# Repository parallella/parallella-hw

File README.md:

PARALLELLA: Supercomputing for Everyone
========================================	

This repository contains open source board and FPGA designs associated with the Parallella project. 

## Directory

Board                                | Description                | CAD       | Status     |
-------------------------------------|----------------------------|-----------|------------|
[parallella](parallella/README.md)   | Parallella                 | Cadence   | Production |
[porcupine](porcupine/README.md)     | Parallella Breakout Board  | KiCad     | Production |
[meta](meta)                         | Epiphany 4096-core System  | Cadence   | Prototype  |
[buddy](buddy)                       | Epiphany-V Evaluation Board| Cadence   | Prototype  |
[paracase](paracase)                 | Aluminum Case              | SolidWorks| Production |
[parasdr](parasdr/README.md)         | SDR adapter Board          | Cadence   | Production |
[kvision](kvision/README.md)         | Stereo Vision Board        | Altium    | Prototype  |
[paralime](paralime)                 | Myriad-RF daughter Board   | KiCad     | Prototype  |
[paracluster](paracluster/README.md) | Cluster Board              | N/A       | Prototype  |
[paralib](paralib)                   | CAD librares               | Various   | Prouction  |
[paratemplate](paratemplate)         | Daugher Card Template      | KiCad     | Production |
[paratile](paratile/README.md)       | Breakout Board             | Eagle     | Prototype  |
[aafm](aafm/README.md)               | Epiphany-III FMC Board     | KiCad     | Production |
[archive](archive)                   | Old Parallella stuff       | N/A       | Obsolete   |

## FPGA Design Sources
All Parallella related FPGA sources have been moved to the [OH! library](https://github.com/parallella/oh) library and released under MIT license.

## License
Board design files are released under the Creative Common Share Alike license unlesss otherwise specified.

## How to do a pull-request

1. Fork this repository to your personal github account using the 'fork' button 2. above
3. Clone your 'parallella-hw' fork to a local computer using 'git clone'
4. Create a new sub-directory at the root of the repo
5. Add your project files with the appropriate license clearly stated
6. Add a README.md file (see the skeleton directory for a template)
7. Use git add-->git commit-->git push to add changes to your fork of 'parallella-examples'
8. Submit a pull request by clicking the 'pull request' button on YOUR github 'parallella-examples' repo.

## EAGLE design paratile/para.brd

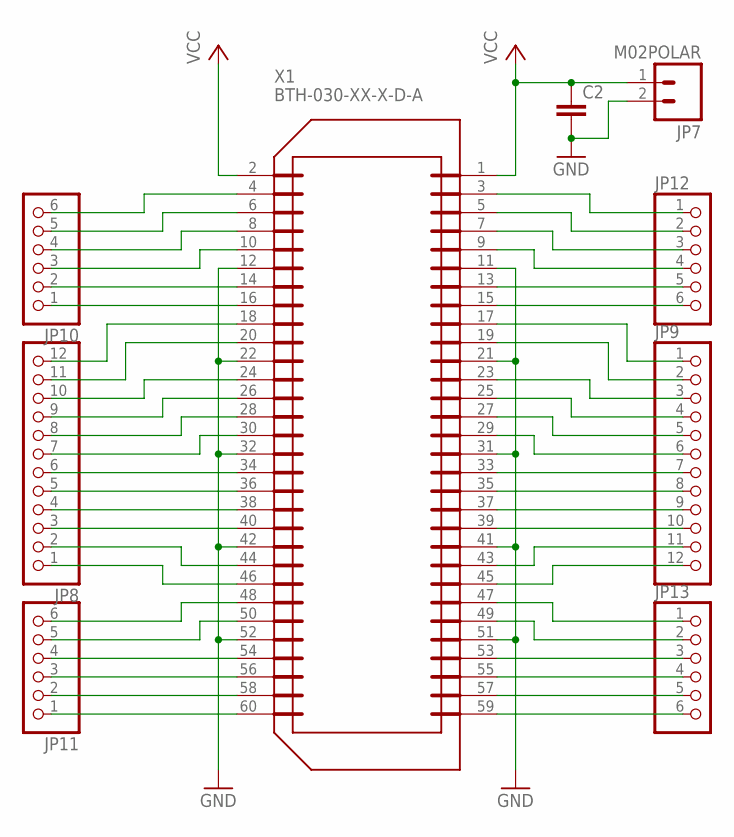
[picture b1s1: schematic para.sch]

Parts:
C2: CAP0805; 0805
JP7: M02POLAR; MOLEX-1X2
JP8, JP9: PINHD-1X12-CB; 1X12-CB
JP10, JP11, JP12, JP13: PINHD-1X6CB; 1X06-CLEANBIG
X1: BTH-030-XX-X-D-A

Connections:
GND: C2.2, JP7.2, X1.11, X1.12, X1.21, X1.22, X1.31, X1.32, X1.41, X1.42, X1.51, X1.52
GPIO0_N: JP12.1, X1.3
GPIO0_P: JP12.2, X1.5
GPIO1_N: JP10.6, X1.4
GPIO1_P: JP10.5, X1.6
GPIO2_N: JP12.3, X1.7
GPIO2_P: JP12.4, X1.9
GPIO3_N: JP10.4, X1.8
GPIO3_P: JP10.3, X1.10
GPIO4_N: JP12.5, X1.13
GPIO4_P: JP12.6, X1.15
GPIO5_N: JP10.2, X1.14
GPIO5_P: JP10.1, X1.16
GPIO6_N: JP9.1, X1.17
GPIO6_P: JP9.2, X1.19
GPIO7_N: JP8.12, X1.18
GPIO7_P: JP8.11, X1.20
GPIO8_N: JP9.3, X1.23
GPIO8_P: JP9.4, X1.25
GPIO9_N: JP8.10, X1.24
GPIO9_P: JP8.9, X1.26
GPIO10_N: JP9.5, X1.27
GPIO10_P: JP9.6, X1.29
GPIO11_N: JP8.8, X1.28
GPIO11_P: JP8.7, X1.30
GPIO12_N: JP9.7, X1.33
GPIO12_P: JP9.8, X1.35
GPIO13_N: JP8.6, X1.34
GPIO13_P: JP8.5, X1.36
GPIO14_N: JP9.9, X1.37
GPIO14_P: JP9.10, X1.39
GPIO15_N: JP8.4, X1.38
GPIO15_P: JP8.3, X1.40
GPIO16_N: JP9.11, X1.43
GPIO16_P: JP9.12, X1.45
GPIO17_N: JP8.2, X1.44
GPIO17_P: JP8.1, X1.46
GPIO18_N: JP13.1, X1.47
GPIO18_P: JP13.2, X1.49
GPIO19_N: JP11.6, X1.48
GPIO19_P: JP11.5, X1.50
GPIO20_N: JP13.3, X1.53
GPIO20_P: JP13.4, X1.55
GPIO21_N: JP11.4, X1.54
GPIO21_P: JP11.3, X1.56
GPIO22_N: JP13.5, X1.57
GPIO22_P: JP13.6, X1.59
GPIO23_N: JP11.2, X1.58
GPIO23_P: JP11.1, X1.60
VCC: C2.1, JP7.1, X1.1, X1.2

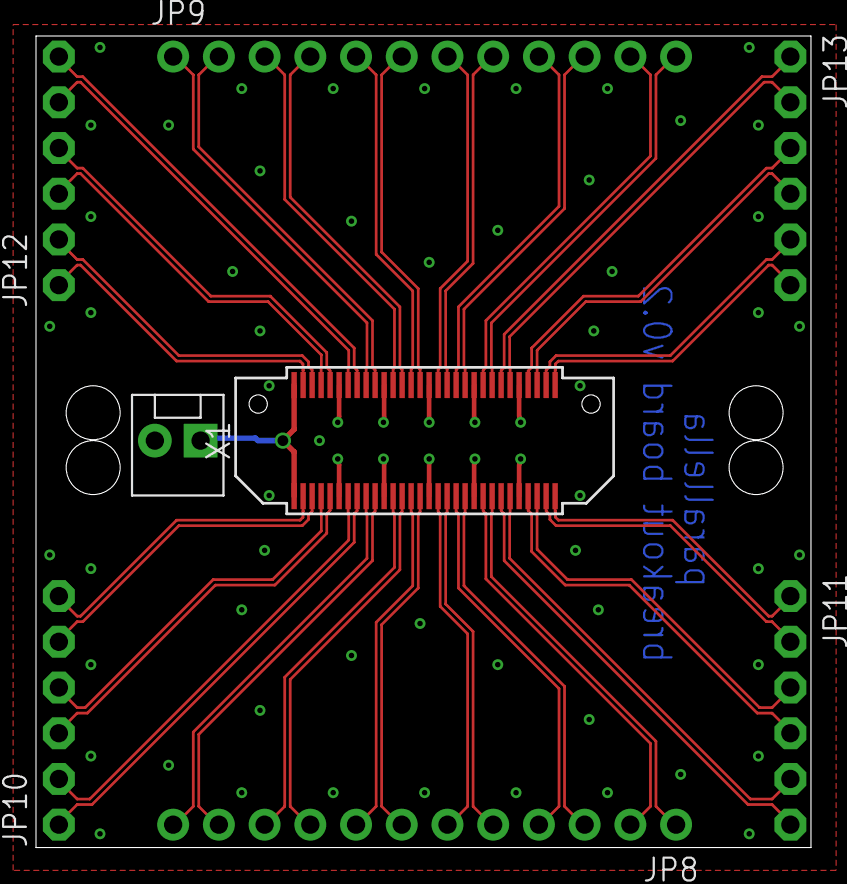
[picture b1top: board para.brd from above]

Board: 2 copper layers, 43.1 x 45.1 mm, 9 parts (1 on the bottom side), 50 nets.

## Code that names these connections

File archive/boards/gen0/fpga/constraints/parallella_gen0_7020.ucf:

#######################
# HDMI constraints
#######################

NET HDMI_D8  	    LOC = Y18  | IOSTANDARD = LVCMOS25;
NET HDMI_D9  	    LOC = W18  | IOSTANDARD = LVCMOS25;
NET HDMI_D10 	    LOC = V18  | IOSTANDARD = LVCMOS25;
NET HDMI_D11 	    LOC = U18  | IOSTANDARD = LVCMOS25;
NET HDMI_D12 	    LOC = R18  | IOSTANDARD = LVCMOS25;
NET HDMI_D13 	    LOC = P18  | IOSTANDARD = LVCMOS25;
NET HDMI_D14 	    LOC = Y19  | IOSTANDARD = LVCMOS25;
NET HDMI_D15 	    LOC = W19  | IOSTANDARD = LVCMOS25;
NET HDMI_D16 	    LOC = U19  | IOSTANDARD = LVCMOS25;
NET HDMI_D17 	    LOC = T19  | IOSTANDARD = LVCMOS25;
NET HDMI_D18 	    LOC = R19  | IOSTANDARD = LVCMOS25;
NET HDMI_D19 	    LOC = P19  | IOSTANDARD = LVCMOS25;
NET HDMI_D20 	    LOC = W20  | IOSTANDARD = LVCMOS25;
NET HDMI_D21 	    LOC = V20  | IOSTANDARD = LVCMOS25;
NET HDMI_D22 	    LOC = U20  | IOSTANDARD = LVCMOS25;   
NET HDMI_D23 	    LOC = T20  | IOSTANDARD = LVCMOS25;
NET HDMI_CLK        LOC = R17  | IOSTANDARD = LVCMOS25;
NET HDMI_VSYNC      LOC = V17  | IOSTANDARD = LVCMOS25;
NET HDMI_HSYNC      LOC = T17  | IOSTANDARD = LVCMOS25;
NET HDMI_DE         LOC = Y17  | IOSTANDARD = LVCMOS25;
#NET HDMI_SPDIF      LOC = Y16  | IOSTANDARD = LVCMOS25;
#NET TURBO_MODE      LOC = R16  | IOSTANDARD = LVCMOS25;

NET PS_I2C_SCL      LOC = N18  | IOSTANDARD = LVCMOS25;
NET PS_I2C_SDA      LOC = N17  | IOSTANDARD = LVCMOS25;

#####################
# Epiphany Interface
#####################
# cclk
NET "RXI_CCLK_P" LOC = "N20" | IOSTANDARD = LVDS_25;
NET "RXI_CCLK_N" LOC = "P20" | IOSTANDARD = LVDS_25;
# reset
NET "DSP_RESET_N" LOC = "G14" | IOSTANDARD = LVCMOS25;
# flag
NET "DSP_FLAG" LOC = "J15" | IOSTANDARD = LVCMOS25;
# rxi lclk 
NET "RXI_LCLK_P" LOC = "F16" | IOSTANDARD = LVDS_25;
NET "RXI_LCLK_N" LOC = "F17" | IOSTANDARD = LVDS_25;
# rxi data
NET "RXI_DATA0_P" LOC = "B19" | IOSTANDARD = LVDS_25;
NET "RXI_DATA0_N" LOC = "A20" | IOSTANDARD = LVDS_25;
NET "RXI_DATA1_P" LOC = "C20" | IOSTANDARD = LVDS_25;
NET "RXI_DATA1_N" LOC = "B20" | IOSTANDARD = LVDS_25;
NET "RXI_DATA2_P" LOC = "D19" | IOSTANDARD = LVDS_25;
NET "RXI_DATA2_N" LOC = "D20" | IOSTANDARD = LVDS_25;
NET "RXI_DATA3_P" LOC = "E18" | IOSTANDARD = LVDS_25;
NET "RXI_DATA3_N" LOC = "E19" | IOSTANDARD = LVDS_25;
NET "RXI_DATA4_P" LOC = "E17" | IOSTANDARD = LVDS_25;
NET "RXI_DATA4_N" LOC = "D18" | IOSTANDARD = LVDS_25;
NET "RXI_DATA5_P" LOC = "F19" | IOSTANDARD = LVDS_25;
NET "RXI_DATA5_N" LOC = "F20" | IOSTANDARD = LVDS_25;
NET "RXI_DATA6_P" LOC = "G17" | IOSTANDARD = LVDS_25;
NET "RXI_DATA6_N" LOC = "G18" | IOSTANDARD = LVDS_25;
NET "RXI_DATA7_P" LOC = "G19" | IOSTANDARD = LVDS_25;
NET "RXI_DATA7_N" LOC = "G20" | IOSTANDARD = LVDS_25;
#rxi frame
NET "RXI_FRAME_P" LOC = "H15" | IOSTANDARD = LVDS_25;
NET "RXI_FRAME_N" LOC = "G15" | IOSTANDARD = LVDS_25;
#rxo waits
NET "RXO_RD_WAIT_P" LOC = "H16" | IOSTANDARD = LVDS_25;
NET "RXO_RD_WAIT_N" LOC = "H17" | IOSTANDARD = LVDS_25;
NET "RXO_WR_WAIT_P" LOC = "J18" | IOSTANDARD = LVDS_25;
NET "RXO_WR_WAIT_N" LOC = "H18" | IOSTANDARD = LVDS_25;
# txo lclk 
#NET "TXO_LCLK_P" LOC = "L14" | IOSTANDARD = LVDS_25; switch with data1
#NET "TXO_LCLK_N" LOC = "L15" | IOSTANDARD = LVDS_25;
NET "TXO_LCLK_P" LOC = "K17" | IOSTANDARD = LVDS_25;
NET "TXO_LCLK_N" LOC = "K18" | IOSTANDARD = LVDS_25;
# txo data
NET "TXO_DATA0_P" LOC = "K19" | IOSTANDARD = LVDS_25;
NET "TXO_DATA0_N" LOC = "J19" | IOSTANDARD = LVDS_25;
#NET "TXO_DATA1_P" LOC = "K17" | IOSTANDARD = LVDS_25; switch with lclk
#NET "TXO_DATA1_N" LOC = "K18" | IOSTANDARD = LVDS_25;
NET "TXO_DATA1_P" LOC = "L14" | IOSTANDARD = LVDS_25;
NET "TXO_DATA1_N" LOC = "L15" | IOSTANDARD = LVDS_25;
NET "TXO_DATA2_P" LOC = "L16" | IOSTANDARD = LVDS_25;
NET "TXO_DATA2_N" LOC = "L17" | IOSTANDARD = LVDS_25;
NET "TXO_DATA3_P" LOC = "M14" | IOSTANDARD = LVDS_25;
NET "TXO_DATA3_N" LOC = "M15" | IOSTANDARD = LVDS_25;
NET "TXO_DATA4_P" LOC = "L19" | IOSTANDARD = LVDS_25;
NET "TXO_DATA4_N" LOC = "L20" | IOSTANDARD = LVDS_25;
NET "TXO_DATA5_P" LOC = "M19" | IOSTANDARD = LVDS_25;
NET "TXO_DATA5_N" LOC = "M20" | IOSTANDARD = LVDS_25;
NET "TXO_DATA6_P" LOC = "M17" | IOSTANDARD = LVDS_25;
NET "TXO_DATA6_N" LOC = "M18" | IOSTANDARD = LVDS_25;
NET "TXO_DATA7_P" LOC = "N15" | IOSTANDARD = LVDS_25;
NET "TXO_DATA7_N" LOC = "N16" | IOSTANDARD = LVDS_25;
#txo frame
NET "TXO_FRAME_P" LOC = "J20" | IOSTANDARD = LVDS_25;
NET "TXO_FRAME_N" LOC = "H20" | IOSTANDARD = LVDS_25;
#txi waits
NET "TXI_RD_WAIT_P" LOC = "K14" | IOSTANDARD = LVDS_25;
NET "TXI_RD_WAIT_N" LOC = "J14" | IOSTANDARD = LVDS_25;
NET "TXI_WR_WAIT_P" LOC = "K16" | IOSTANDARD = LVDS_25;
NET "TXI_WR_WAIT_N" LOC = "J16" | IOSTANDARD = LVDS_25;

#######################
# GPIO
#######################
NET "GPIO0_P"  LOC = "T16" | IOSTANDARD = LVDS_25;
NET "GPIO0_N"  LOC = "U17" | IOSTANDARD = LVDS_25;
NET "GPIO1_P"  LOC = "V16" | IOSTANDARD = LVDS_25;
NET "GPIO1_N"  LOC = "W16" | IOSTANDARD = LVDS_25;
NET "GPIO2_P"  LOC = "P15" | IOSTANDARD = LVDS_25;
NET "GPIO2_N"  LOC = "P16" | IOSTANDARD = LVDS_25;
NET "GPIO3_P"  LOC = "V15" | IOSTANDARD = LVDS_25;
NET "GPIO3_N"  LOC = "W15" | IOSTANDARD = LVDS_25;
NET "GPIO4_P"  LOC = "P14" | IOSTANDARD = LVDS_25;
NET "GPIO4_N"  LOC = "R14" | IOSTANDARD = LVDS_25;
NET "GPIO5_P"  LOC = "T14" | IOSTANDARD = LVDS_25;
NET "GPIO5_N"  LOC = "T15" | IOSTANDARD = LVDS_25;
NET "GPIO6_P"  LOC = "U14" | IOSTANDARD = LVDS_25;
NET "GPIO6_N"  LOC = "U15" | IOSTANDARD = LVDS_25;
NET "GPIO7_P"  LOC = "W14" | IOSTANDARD = LVDS_25;
NET "GPIO7_N"  LOC = "Y14" | IOSTANDARD = LVDS_25;
NET "GPIO8_P"  LOC = "U13" | IOSTANDARD = LVDS_25;
NET "GPIO8_N"  LOC = "V13" | IOSTANDARD = LVDS_25;
NET "GPIO9_P"  LOC = "V12" | IOSTANDARD = LVDS_25;
NET "GPIO9_N"  LOC = "W13" | IOSTANDARD = LVDS_25;
NET "GPIO10_P" LOC = "T12" | IOSTANDARD = LVDS_25;
NET "GPIO10_N" LOC = "U12" | IOSTANDARD = LVDS_25;
NET "GPIO11_P" LOC = "T11" | IOSTANDARD = LVDS_25;
NET "GPIO11_N" LOC = "T10" | IOSTANDARD = LVDS_25;

##################################
# IOs to be used with zc7020 ONLY
##################################
NET "GPIO12_P" LOC = "Y12" | IOSTANDARD = LVDS_25;
NET "GPIO12_N" LOC = "Y13" | IOSTANDARD = LVDS_25;
NET "GPIO13_P" LOC = "W11" | IOSTANDARD = LVDS_25;
NET "GPIO13_N" LOC = "Y11" | IOSTANDARD = LVDS_25;
NET "GPIO14_P" LOC = "V11" | IOSTANDARD = LVDS_25;
NET "GPIO14_N" LOC = "V10" | IOSTANDARD = LVDS_25;
NET "GPIO15_P" LOC = "T9"  | IOSTANDARD = LVDS_25;
NET "GPIO15_N" LOC = "U10" | IOSTANDARD = LVDS_25;
NET "GPIO16_P" LOC = "W10" | IOSTANDARD = LVDS_25;
NET "GPIO16_N" LOC = "W9"  | IOSTANDARD = LVDS_25;
NET "GPIO17_P" LOC = "U9"  | IOSTANDARD = LVDS_25;
NET "GPIO17_N" LOC = "U8"  | IOSTANDARD = LVDS_25;
NET "GPIO18_P" LOC = "V8"  | IOSTANDARD = LVDS_25;
NET "GPIO18_N" LOC = "W8"  | IOSTANDARD = LVDS_25;
NET "GPIO19_P" LOC = "Y9"  | IOSTANDARD = LVDS_25;
NET "GPIO19_N" LOC = "Y8"  | IOSTANDARD = LVDS_25;
NET "GPIO20_P" LOC = "Y7"  | IOSTANDARD = LVDS_25;
NET "GPIO20_N" LOC = "Y6"  | IOSTANDARD = LVDS_25;
NET "GPIO21_P" LOC = "U7"  | IOSTANDARD = LVDS_25;
NET "GPIO21_N" LOC = "V7"  | IOSTANDARD = LVDS_25;
NET "GPIO22_P" LOC = "V6"  | IOSTANDARD = LVDS_25;
NET "GPIO22_N" LOC = "W6"  | IOSTANDARD = LVDS_25;
NET "GPIO23_P" LOC = "T5"  | IOSTANDARD = LVDS_25;
NET "GPIO23_N" LOC = "U5"  | IOSTANDARD = LVDS_25;

#######################
# Internal constraints
#######################
NET "TXO_LCLK_P" TNM_NET = "TXO_LCLK_P";
TIMESPEC "TS_TXO_LCLK_P" = PERIOD "TXO_LCLK_P" 6.6ns HIGH 50% INPUT_JITTER 100ps;

NET "parallella/ewrapper_link_top/io_tx/CLK_IN" TNM_NET = "CLK_IN";
TIMESPEC "TS_CLK_IN" = PERIOD "CLK_IN" 10ns HIGH 50% INPUT_JITTER 100ps;

NET "parallella/ewrapper_link_top/io_tx/CLK_IN_90" TNM_NET = "CLK_FWD_IN";
TIMESPEC "TS_CLK_FWD_IN" = PERIOD "CLK_FWD_IN" 10ns HIGH 50% INPUT_JITTER 100ps;

INST "parallella/axi_elink_if/fpgacfg/reset_chip_reg_4" TNM = "SW_RESET";
TIMESPEC "TS_SW_RESET" = FROM "SW_RESET" TIG;

#INST "rst_sync*" ASYNC_REG = TRUE;
#PIN "CLK_RESET" TIG;
#PIN "IO_RESET" TIG;

NET "system_stub/system_i/processing_system7_0/FCLK_CLK3" TNM_NET = clk_fpga_3;
TIMESPEC TS_clk_fpga_3 = PERIOD clk_fpga_3 40000 kHz;

NET "system_stub/system_i/processing_system7_0/FCLK_CLK2" TNM_NET = clk_fpga_2;
TIMESPEC TS_clk_fpga_2 = PERIOD clk_fpga_2 200000 kHz;

NET "system_stub/system_i/processing_system7_0/FCLK_CLK1" TNM_NET = clk_fpga_1;
TIMESPEC TS_clk_fpga_1 = PERIOD clk_fpga_1 200000 kHz;

NET "system_stub/system_i/processing_system7_0/FCLK_CLK0" TNM_NET = clk_fpga_0;
TIMESPEC TS_clk_fpga_0 = PERIOD clk_fpga_0 100000 kHz;

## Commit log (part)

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2013-06-29 Initial repository creation
2013-07-03 Change schematic pdf name to avoid confusion
2013-07-11 Fixed Reg_en issue Added pull-up/down transistors on elink frame signals to avoid spurious transacftions Renamed a few pec_power signals Changed Intersil part number
2013-08-09 Changed to conforming name
2013-08-27 Added gen0 fpga design files, work in progress..
2013-08-30 Removed duplicate files (can be found in comon hdl)
2013-08-30 Removed duplicate file, added license
2013-08-30 Added .gitignore file to prepare for putting in project files
2013-08-31 HDMI support thanks to Antmicro contribution.
2013-09-23 Updated constraints file for Gen1
2013-10-10 changed RXO_RD_WAIT to single ended signal
2013-10-10 Made RXO_RD_WAIT signal single ended(removed diff buffer)
2013-11-26 Parallella "Gen1.1" Files added
2013-11-26 Removed garbage file
2014-01-24 More repository cleanup..
2014-01-24 Latest Parallella Gen1.2 changes, added safe fix for USB power issue.
2014-01-24 Updated boot images
2014-01-24 Clarification
2014-03-13 Started reorganization.
2014-03-14 Added / changed ignore rules, added runs directory to avoid errors from planAhead.
2014-03-14 Reset run data to match empty impl and synth dirs.
2014-03-19 set / clear, it's only off by 1.
2014-03-21 Cleaned-up timing issue for E64. Had to change to manual compile order for E16 project.
2014-03-26 Added 7010 project, renamed top-level file to fit w/7010 or 7020 projects, split ucf files into generic placement, 7020 extra pins, and timing. Added project-level READMEs.
2014-03-26 Markdown updates 2
2014-04-08 Updated recommended ISE version
2014-04-13 Added I2C interface to all projects, will always work for u-boot but will not be available to users unless added to device tree. Changed version register format. Removed 'k' from named defines. Added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
2014-04-18 Added ability to change elink and gpio iostandards.
2014-04-21 Mods for E64, changed version register.
2014-04-21 Bitstreams w/ new version register structure. E64 uses LVDS for eLink. No GPIOs imlemented, but there are still LVDS Rcvrs/Xmtrs on the GPIO pins (12 and 12).
2014-04-28 Minor update to readme.
2014-05-08 Changed the 'fpga/bitstreams' directory to contain board-ready binary files instead of the raw bitfile output of ISE. This is supported by new versions of 'getbits' in each project folder. Note that 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
2014-05-16 Added external repo fpgahdl_xilinx from analog devices. Added helper scripts for external repo fetch & sparse checkout.
2014-05-23 README updates.
2014-05-23 Fixed nested lists.
2014-05-23 Yeah, can't have blockquotes within an ordered list without restarting the count.
2014-06-03 Added E64 project with HDMI. Some cleanup to paracard template.
2014-06-06 First commit of porcupine board, not complete, not routed, don't use!
2014-06-17 Completed design w/3-row XID/YID and various 4-pin IO connectors. Fixed page ordering, changed "Mfr" field to "Manufacturer" Will now re-do to combine all misc. functions onto a single 2xN connector.
2014-06-19 Ready for full review.
2014-06-21 As released for fab., Rev. A.
2014-07-22 Updated flash images & readme instructions.
2014-07-28 Cleanup for Vivado project.
2014-07-29 Add create_project script, don't import PS files into project.
2014-09-02 Step #3 clarification
    Added version and flash to step 3 name to match step 9
2014-10-07 First version of new elink interface
2014-10-11 First version of new elink register file Significantly expanded feature spec: -cclk power down/divider -gpio mod -loopback support -start of irq/mmu feature -traffic monitor
2014-11-03 Adding some memory wrappers (not yet tested)
2014-11-03 Adding a monitor block for elink -tracks wait signals -tracks access signals (not verified)
2014-11-04 Adding a simple dv unit test for configuration file
2014-11-04 Removing interrupt signal
2014-11-05 Adding module for testing the monitor circuit
2014-11-05 Adding generic memory modules -insert tecnology specific macros insides (BRAM etc)
2014-11-05 Lint fix (matching bit widths)
2014-11-06 Run script for embox
2014-11-06 Changed to 20 bit addressing for clarity in FPGA
2014-11-06 Adding run.sh files for simulation
2014-11-06 Adding readback indicator for AXI slave mux
2014-11-06 Basic interfaces..still need to add the axi signals and fill in the content
2014-11-06 Adding place holders for hard macros
2014-11-06 More file organization Adding some more utility functions
2014-11-06 Deleting old files (moved to src)
2014-11-19 Added elink-gold -> elink2 test project.
2014-11-24 Minor fixes for implementation.
2014-12-12 Removing old files not needed by new design
2014-12-12 Changed module name for new structure
2014-12-14 Incremental renaming
2014-12-14 Adding new verilog modules for receiver and transmitter -moving away from Vivado block editor -creating a "clean" split between RX and TX
2014-12-14 Adding README file describing design structure of the elink
2014-12-15 Adding fofo environment for elink to check for broken signals. Too many stub modules to be practical..next need sim models
2014-12-15 Adding stubs files for xilinx IP Goal is to create models for all of these
2014-12-15 Verious silly compilation fixes, nothing to see here..
2014-12-15 Wrong bus width (just cleanup..)
2014-12-15 Fixing port declarations (thanks Verilator!)
2015-01-28 Partial integration of new elink
2015-02-19 Porcupine Version 2.
2015-03-21 Adding the latest Vivado design archive for Parallella
2015-03-23 Includes Fred's latest bug fixes (from project archive)
2015-03-25 Massive checkin... -this may break already broken projects -creates a Verilog top level (instead of using Vivado block level design) -integrates mmy and mailbox (not completely integrated) -compiles.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
2015-04-08 Fixing bus issue with datain/dataout signal Found in Vivado... Needed to connect up the wait signals properly on dataout/datain registers
2015-04-08 Adding constants directory 1. Platform specific constants (xilinx vs altera) 2. Version specific constants Basically anything that affects `ifdefs
2015-04-09 Adding stubs for IP blocks used in elink
2015-04-09 Vivado run through -missed connections -mismatched bus widths -missing IP blocks -cleanup -proper DV starts tomorrow
2015-04-09 Removing unecessary levels of hiearchy
2015-04-09 Reorg, cleanup
2015-04-09 fixed broken links
2015-04-09 Fixing bad merge This block will be completely redesigned
2015-04-10 emmu: Refactor and add verilator testbench
    Testbench is split between the synthesizable transactors and
    non-synthesizable parts to allow reuse of transactors in the newly
    added verilator test bench
2015-04-11 Reorganizing files...too many folders after all. There is only one elink...
2015-04-12 Changing emesh/elink transaction order Our "standard packet" order should be followed everywhere to ease verification and integration (standards are good fir reuse...): [0]=access [1]=write [3:2]=dat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
2015-04-14 Clean up of old files
2015-04-14 Adding missing stubs
2015-04-14 Added "fufu" DV environment for elink -Icarus for now, verilator comes next -Using our "standard" emesh interface ..here we go...
2015-04-14 Verilator lint cleanup ~10 real bugs -mostly name mismatches and bit range mistakes
2015-04-15 Adding back the "common" directory
2015-04-15 Running with "TARGET_CLEAN"
2015-04-15 Adding platform agnostic dual ported memory and async fifo
2015-04-15 Continued work to create clean design: -pll bypass for clocks (customer request) -adding dividers on all clocks (tx/cclk) -adding reset block (clearer) -using commong clock_divider block -need to cle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
2015-04-15 Fixing startup issues in transmit path: -adding reset signals to synchronizer to solve startup issues -setting config in test bench for speedup, default reg config now correct -fix (my) stupid bug in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
2015-04-15 Xilinx models -adding ODDR model -configuring the ecfg (rx/tx/clk) in testbench
2015-04-16 Renaming to something more clear (per user input...)
2015-04-17 Changing ESYSCLK definition (again.....) old implementation felt too "cutsy" this makes for a cleaner usage model (simple shift with param) also splitting out enable but, not making the CTIMER mistak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
2015-04-17 Fixed odd/even copy past bug on DDR sampler
2015-04-17 MILESTONE: Open souce simulation elink loopback working!
2015-04-18 Adding documentation to elink top level module
2015-04-18 Spell checking comments First time ever using spell cheker in EMACS. Hard to believe...but it's true! I am sure this speaks volume for how little I have commented my code over the years!
2015-04-18 Prettifying format..starting to look decent
2015-04-18 Adding high level single ported memory
2015-04-18 Clock divider fixup -changed to latest and hopefully final register config -fixed functional bugs (was broken..) -added xor for sensing change of clock frequency
2015-04-18 Removed synchronizer on TXLCLK
2015-04-18 Changed register map -Moved "groups" to E,D,C -Changed names to EL* (shorter is better, clear enough) -Moved order to fit logical operation during init -Moved embox registers to MMR group DONE!
2015-04-18 Clock cleanup -Adding enable signal to clock out. Definitely right decision to keep separate bit from the divider field. -Fixed settings for to fit new register field -XILINX version is still broken!!
2015-04-18 Adding gtkwave signals file
2015-04-20 MMU working... -Needs more testing
2015-04-21 Adding emesh memory module (empty for now)
2015-04-21 Wrong port direction on output
2015-04-21 Rename
2015-04-21 Added wait signal for reads
2015-04-21 Adding test for readback from host
2015-05-23 Add ESDK 2015.1 compatible bitstreams
    These are the ones used in Pubuntu 2015.1
2015-06-24 Adding smaller logo
2015-06-24 Added logo
2016-02-03 Adding PCI-104 Parallella board -Work in progress, more news later -Comments appreciated!
2016-02-03 Adding incomplete parallella-rf board -Uses AD9361 -Started by Fred Huettig
2016-02-03 Consolidating the community hw repo
2016-02-04 Adding PR instructions
2016-02-04 Restoring README file
2016-02-04 Fixed errors..sigh
2016-02-04 Adding status field -Important to show status to built trust
2016-03-01 Adding datasheets folder for convenience
2016-04-11 Copyright transfer - Assigning license to the non-profit Parallella Foundation
2016-04-27 Adding bringup pictures for kvision (from Emil)
2016-05-20 Adding README for porcupine
2016-05-20 Adding README and explicit license for porcupine
2016-05-20 Cleanup top README links
2016-05-20 Adding lime rf board
2016-08-26 Cleaning up meta/4k specs
2016-09-23 Adding AAFM Epiphany FMC board to repository
2016-10-14 Adding meta pinout file
2016-10-21 Updating pinout for meta -Need separate height connector for control
2016-11-23 Adding porcupine product shots
2016-11-23 Adding gerbers
2016-11-23 Adding physical case picture
2016-12-28 Adding Porcupine pinout diagram -Git tired of having to look through schematics...
2016-12-28 fix type in readme
2016-12-28 Fixing typo on south connector diagram (thanks Twitter!)
2016-12-30 Reorg of sdr project
2017-01-08 Cleaning up olad files
2017-01-08 Formatting again...
2017-01-08 Contributing the buddy open source evaluation board
2017-05-18 Fix BOM for meta module - remove resistors as appropriate to set coordinates - DNP for certain features
2017-05-18 Adding pick and place for parasdr
2017-06-10 Fixing BOM. Wrong samtec connector was omitted !!!!!
2017-07-09 Fixed BOM for E5 buddy board
2017-08-06 Reviewing BOM. Fixing 4 parts errors. You have got to be fu*king kidding me!!!!
2017-09-30 Adding schematics
2017-10-01 Splitting module and carrier for meta -Separate boards -Cleaner split, more consistent
2017-10-01 Cleanup old files
2018-01-27 Adding more dataseet references
2018-04-23 Fixes to various meta board issues -oscillator value -5V rail resistor changes -Added FMC connector -DNPs for throug-holes (mechanical clearance issues) -fixed voltage ratings on capacitors for 12V r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
2018-06-11 Adding a KiCad symbols library for Samtec connector

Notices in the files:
parts and their libraries:
SparkFun-Connectors: Licensing: Creative Commons ShareAlike 4.0 International - https://creativecommons.org/licenses/by-sa/4.0
